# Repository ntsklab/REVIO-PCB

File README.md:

# REVIO-PCB
無保証。
お問い合わせは Twitter @nt776

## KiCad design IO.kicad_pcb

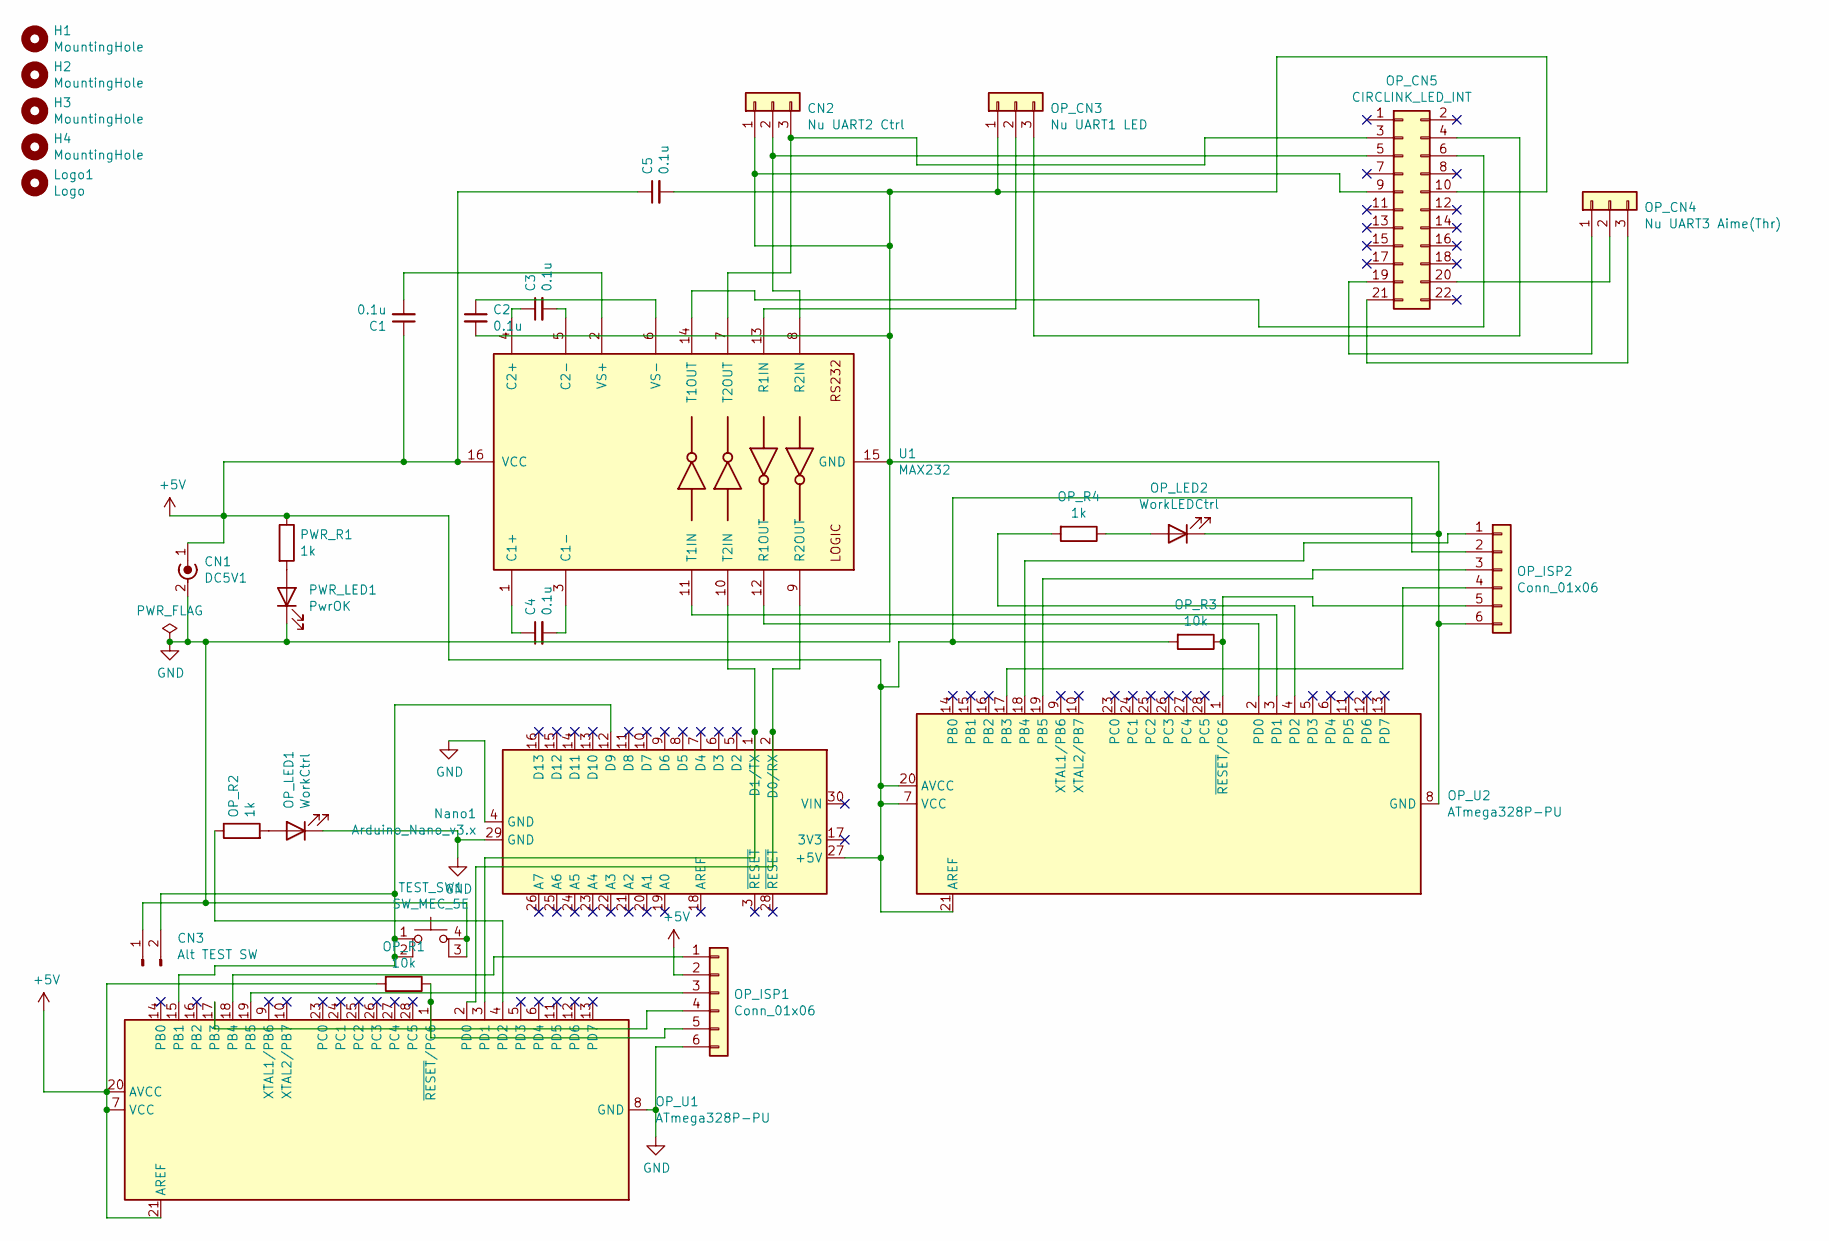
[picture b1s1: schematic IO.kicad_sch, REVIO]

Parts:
C1, C2, C3, C4, C5: 0.1u; C_Disc_D5.0mm_W2.5mm_P5.00mm
CN1: DC5V1; BarrelJack_Horizontal
CN2: Nu UART2 Ctrl; JST_XH_B3B-XH-A_1x03_P2.50mm_Vertical
CN3: Alt TEST SW; JST_XH_B2B-XH-A_1x02_P2.50mm_Vertical
H1, H2, H3, H4: MountingHole; MountingHole_3.2mm_M3
Logo1: Logo; revio
Nano1: Arduino_Nano_v3.x; Arduino_Nano
OP_CN3: Nu UART1 LED; JST_XH_B3B-XH-A_1x03_P2.50mm_Vertical
OP_CN4: Nu UART3 Aime(Thr); JST_XH_B3B-XH-A_1x03_P2.50mm_Vertical
OP_CN5: CIRCLINK_LED_INT; JST_XAD_B22B-XADSS-N_2x11_P2.50mm_Vertical
OP_ISP1, OP_ISP2: Conn_01x06; PinHeader_2x03_P2.54mm_Vertical
OP_LED1: WorkCtrl; LED_D3.0mm
OP_LED2: WorkLEDCtrl; LED_D3.0mm
OP_R1, OP_R3: 10k; R_Axial_DIN0207_L6.3mm_D2.5mm_P10.16mm_Horizontal
OP_R2, OP_R4: 1k; R_Axial_DIN0207_L6.3mm_D2.5mm_P10.16mm_Horizontal
OP_U1, OP_U2: ATmega328P-PU; DIP-28_W7.62mm
PWR_LED1: PwrOK; LED_D3.0mm
PWR_R1: 1k; R_Axial_DIN0207_L6.3mm_D2.5mm_P10.16mm_Horizontal
TEST_SW1: SW_MEC_5E; SW_TH_Tactile_Omron_B3F-10xx
U1: MAX232; DIP-16_W7.62mm

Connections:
+5V: C1.1, C5.1, CN1.1 (In), Nano1.27 (+5V), OP_ISP1.2, OP_ISP2.2, OP_R1.2, OP_R3.2, OP_U1.7 (VCC), OP_U1.20 (AVCC), OP_U1.21 (AREF), OP_U2.7 (VCC), OP_U2.20 (AVCC), OP_U2.21 (AREF), PWR_R1.1, U1.16 (VCC)
GND: C2.2, C5.2, CN1.2 (Ext), CN2.1, CN3.1, Nano1.4 (GND), Nano1.29 (GND), OP_CN3.1, OP_CN5.9, OP_CN5.10, OP_ISP1.6, OP_ISP2.6, OP_LED1.1 (K), OP_LED2.1 (K), OP_U1.8 (GND), OP_U1.22 (GND), OP_U2.8 (GND), OP_U2.22 (GND), PWR_LED1.1 (K), TEST_SW1.3 (K), TEST_SW1.4 (A), U1.15 (GND)
unnamed: C1.2, U1.2 (VS+)
unnamed: C2.1, U1.6 (VS-)
unnamed: C3.1, U1.4 (C2+)
unnamed: C3.2, U1.5 (C2-)
unnamed: C4.1, U1.1 (C1+)
unnamed: C4.2, U1.3 (C1-)
unnamed: CN2.2, OP_CN5.5, U1.8 (R2IN)
unnamed: CN2.3, OP_CN5.3, U1.7 (T2OUT)
unnamed: CN3.2, Nano1.12 (D9), OP_U1.15 (PB1), TEST_SW1.1, TEST_SW1.2
unnamed: Nano1.1 (D1/TX), OP_U1.3 (PD1), U1.10 (T2IN)
unnamed: Nano1.2 (D0/RX), OP_U1.2 (PD0), U1.9 (R2OUT)
unnamed: OP_CN3.2, U1.13 (R1IN)
unnamed: OP_CN3.3, OP_CN5.4
unnamed: OP_CN4.1, OP_CN5.19
unnamed: OP_CN4.2, OP_CN5.20
unnamed: OP_CN4.3, OP_CN5.21
unnamed: OP_CN5.6, U1.14 (T1OUT)
unnamed: OP_ISP1.1, OP_U1.18 (PB4)
unnamed: OP_ISP1.3, OP_U1.19 (PB5)
unnamed: OP_ISP1.4, OP_U1.17 (PB3)
unnamed: OP_ISP1.5, OP_R1.1, OP_U1.1 (~RESET/PC6)
unnamed: OP_ISP2.1, OP_U2.18 (PB4)
unnamed: OP_ISP2.3, OP_U2.19 (PB5)
unnamed: OP_ISP2.4, OP_U2.17 (PB3)
unnamed: OP_ISP2.5, OP_R3.1, OP_U2.1 (~RESET/PC6)
unnamed: OP_LED1.2 (A), OP_R2.2
unnamed: OP_LED2.2 (A), OP_R4.1
unnamed: OP_R2.1, OP_U1.4 (PD2)
unnamed: OP_R4.2, OP_U2.4 (PD2)
unnamed: OP_U2.2 (PD0), U1.12 (R1OUT)
unnamed: OP_U2.3 (PD1), U1.11 (T1IN)
unnamed: PWR_LED1.2 (A), PWR_R1.2

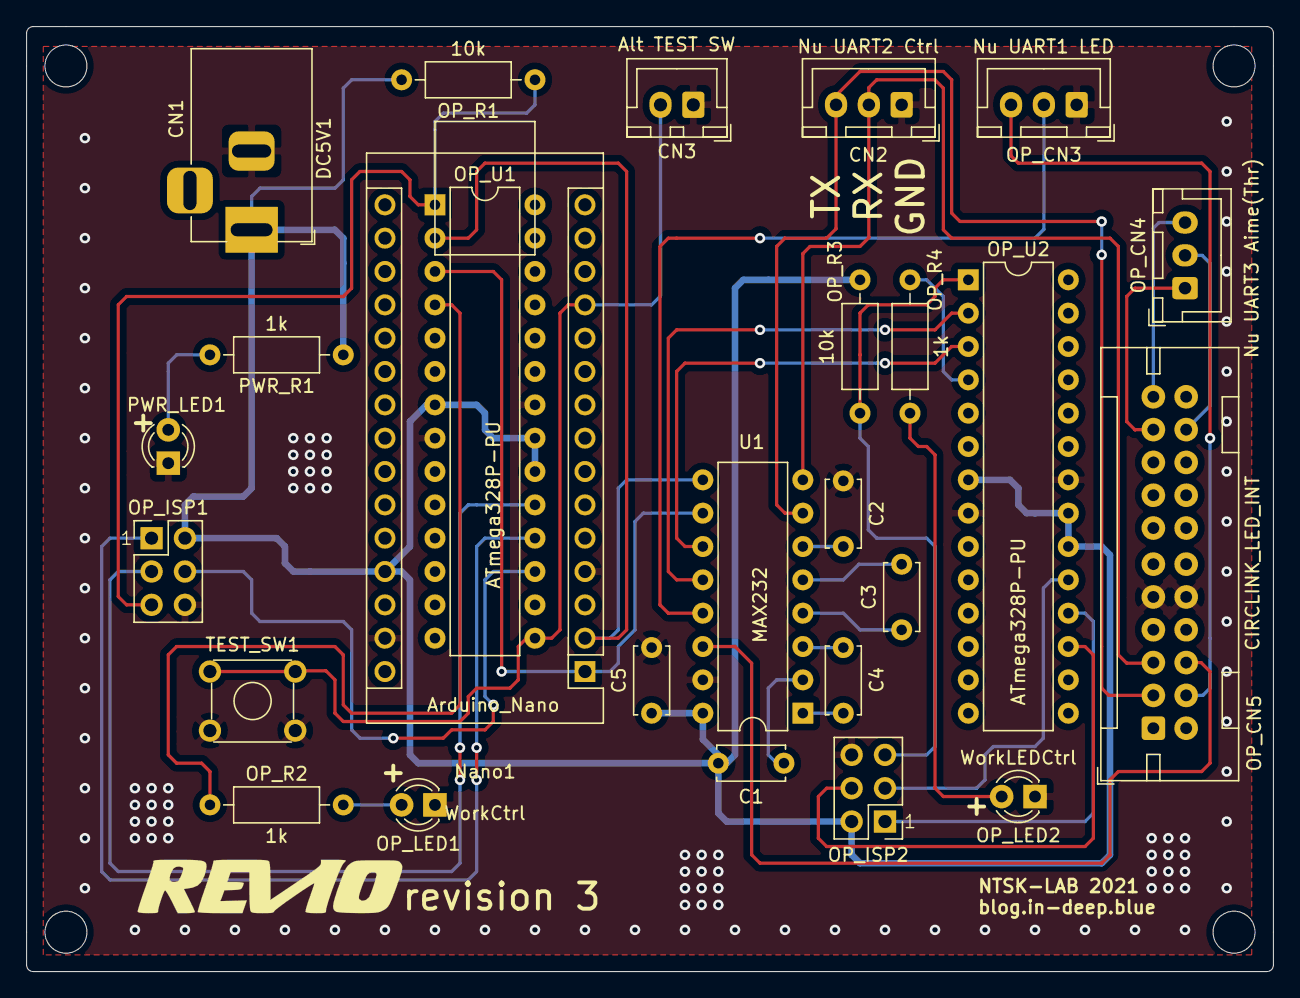
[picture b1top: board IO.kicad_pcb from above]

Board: 2 copper layers, 95.0 x 72.0 mm, 31 parts (0 on the bottom side), 34 nets.

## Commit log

2021-03-20 穴あけ前
2021-03-20 穴あけ後
2021-03-20 Revert "穴あけ後"
    This reverts commit 9a31620a24121a6f974f63edfe8fbebed2765f06.
2021-03-23 Logo changed, Pwr LED moved
2021-03-23 move file
2021-03-25 add xad22, led interrupt circuit
2021-03-25 add arduino replace option
2021-03-25 some change
2021-03-25 r3 beta
2021-05-21 move silk
2022-04-09 kicad 6.x
2022-04-09 remove backups
